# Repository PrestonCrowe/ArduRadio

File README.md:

# ArduRadio

This project includes 3 different projects that are encompased around Arduino-controlled radio chips. 

<br>

I've included the EAGLE PCB files for all of the boards and their respective BOMs besides the V2, but that one uses off the shelf parts so it shouldn't be too hard to make one.

So far, the only board that is 100% complete is the V2 board. I have yet to create any code for the boards. 

TODO
------
Please check the the Projects page on this GitHub page.

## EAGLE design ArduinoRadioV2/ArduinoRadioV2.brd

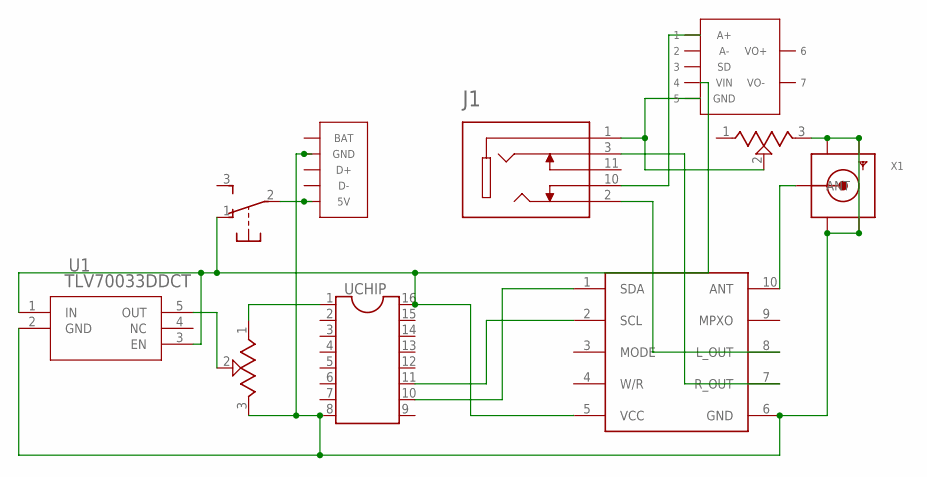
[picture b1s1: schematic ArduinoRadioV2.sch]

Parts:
IC1: UCHIP
J1: SJ1-3525N; CUI_SJ1-3525N
S1: EG1213
TEA5767: TEA5767BREAKOUT; TEA5767MM2
TUNE: 3352T-1-103LF; TRIM_3352T-1-103LF
U1: TLV70033DDCT; DDC5
U$1: AMP
U$2: MICROLIPO
VOL: 3352T-1-103LF; TRIM_3352T-1-103LF
X1: SMACONNECTOR; SMA90_DIP

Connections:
5V: IC1.16 (V_EXT), S1.1 (O), TEA5767.5 (VCC), U1.1 (IN), U1.3 (EN), U$1.VIN (4)
AIN: J1.10, U$1.A+ (1)
ANT: TEA5767.10 (ANT), X1.ANTENNA (ANT)
GND: IC1.8 (GND), TEA5767.6 (GND), TUNE.3 (CW), U1.2 (GND), U$2.P$1 (GND), U$2.P$2 (GND), U$2.P$3 (GND), U$2.P$4 (GND), U$2.P$8 (GND), VOL.3 (CW), X1.GND1, X1.GND2, X1.GND3, X1.GND4
LO: J1.2, TEA5767.8 (L_OUT)
unnamed: IC1.1 (D1/A1), TUNE.1 (CCW)
RO: J1.3, TEA5767.7 (R_OUT)
SCL: IC1.11 (D11), TEA5767.2 (SCL)
SDA: IC1.10 (D10), TEA5767.1 (SDA)
TUNE: TUNE.2 (WIPER), U1.5 (OUT)
VOL: J1.1, U$1.GND (5), VOL.2 (WIPER)
VS: S1.2, U$2.P$5 (5V)

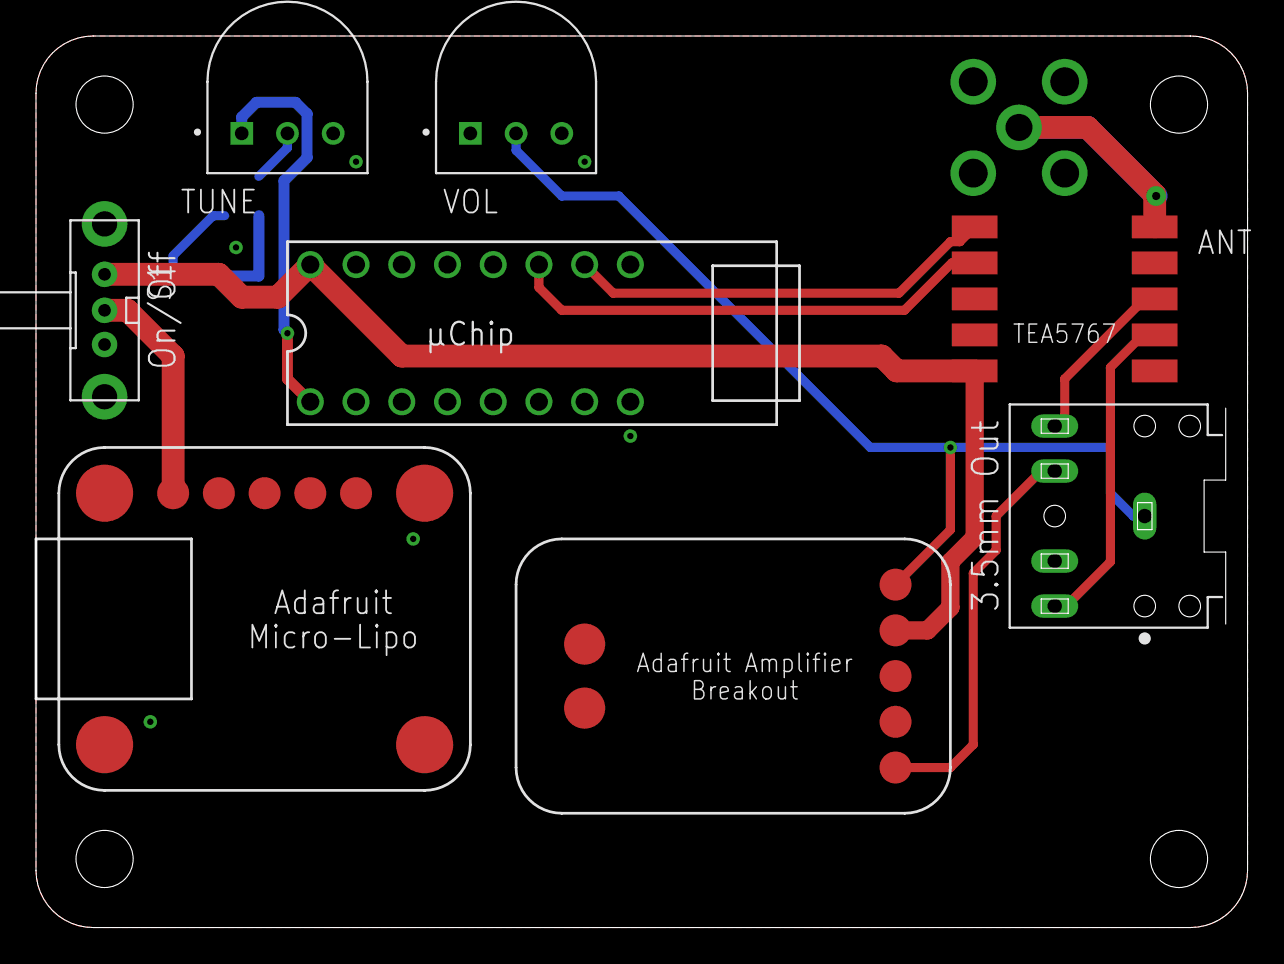
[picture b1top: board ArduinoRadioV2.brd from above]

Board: 2 copper layers, 67.3 x 49.5 mm, 10 parts (1 on the bottom side), 12 nets.

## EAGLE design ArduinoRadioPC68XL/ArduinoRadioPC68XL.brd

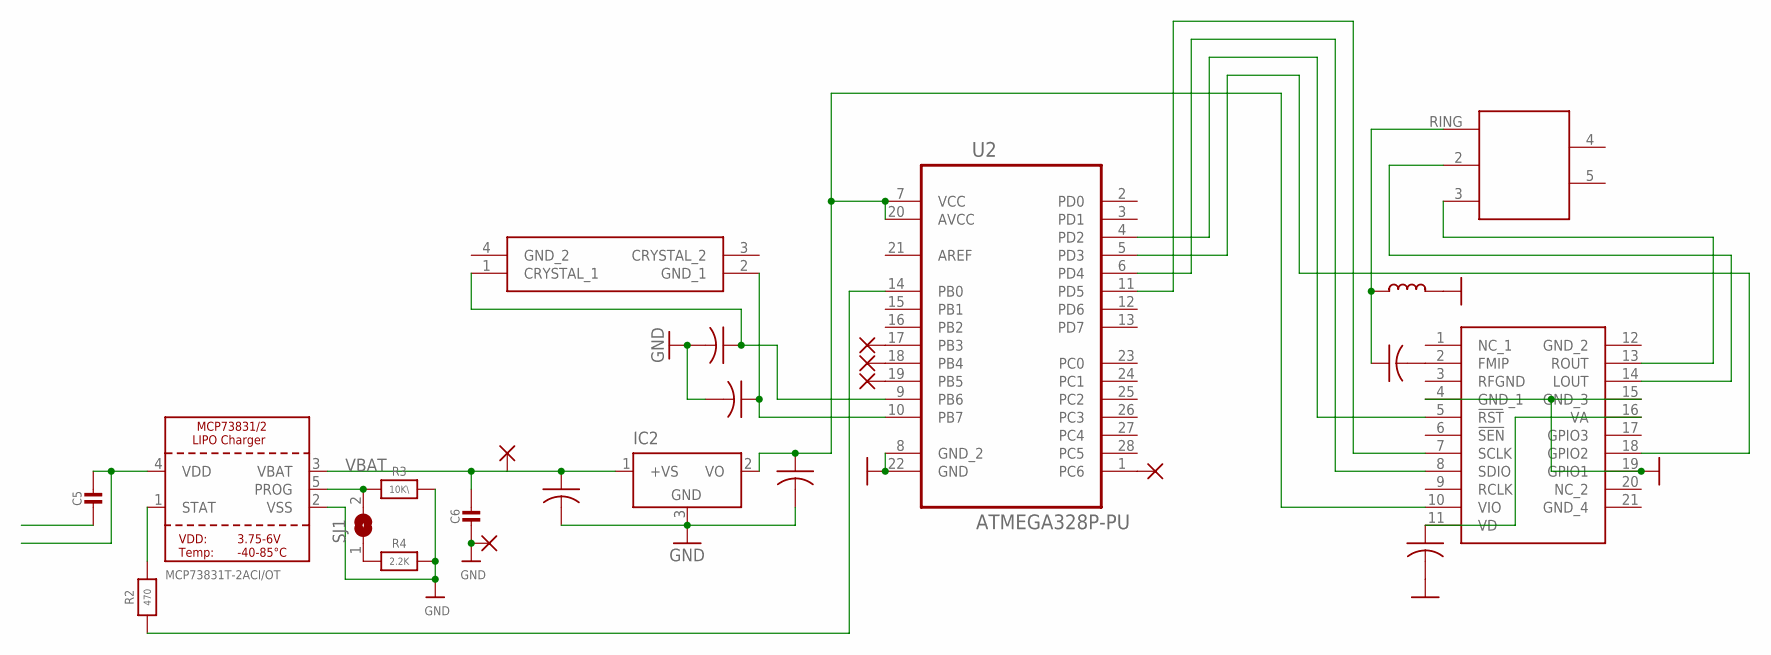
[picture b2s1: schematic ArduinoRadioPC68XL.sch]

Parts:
C1, C2: 10pF; C0402
C3: 47uf; C1206
C4: 47uF; C1206
C5, C6: 10µF; 0805-NO@1
C7: 22nF; C0603
C8: 100pF; C1206
IC2: LM50; SOT23
IC3: SI4703-C19-GM; SI4703C19GM
L1: L_0603; L0603
PAD1, PAD2: WIREPADSMD1,27-254; SMD1,27-2,54
PAD3, PAD4, PAD5, PAD6: SMD2; SMD1,27-2,54
R2: 470; 0603-NO
R3: 10K\; 0603-NO
R4: 2.2K; 0603-NO
SJ1: SOLDERJUMPER; SOLDERJUMPER_ARROW_NOPASTE
U1: MCP73831T-2ACI/OT; SOT23-5
U2: ATMEGA328P-PU; DIP254P762X457-28
U$1: STX-3542-5N-G-TR
Y1: ABM3B-8.000MHZ-10-1-U-T; ABM3B

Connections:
3V3: C4.1, IC2.2 (VO), IC3.10 (VIO), U2.7 (VCC), U2.20 (AVCC)
5V: C5.1, U1.4 (VDD)
ANT: C8.1, L1.2, U$1.RING
GND: C1.2, C2.2, C3.2, C4.2, C5.2, C6.2, C7.2, IC2.3 (GND), IC3.4 (GND_1), IC3.15 (GND_3), IC3.19 (GPIO1), L1.1, PAD2.1, R3.2, R4.2, U1.2 (VSS), U2.8 (GND_2), U2.22 (GND)
GPIO2: IC3.18 (GPIO2), U2.5 (PD3)
LOUT: IC3.14 (LOUT), U$1.2
MISO: PAD5.1, U2.18 (PB4)
MOSI: PAD6.1, U2.17 (PB3)
unnamed: R4.1, SJ1.1
unnamed: C8.2, IC3.2 (FMIP)
PROG: R3.1, SJ1.2, U1.5 (PROG)
RESET: PAD3.1, U2.1 (PC6)
ROUT: IC3.13 (ROUT), U$1.3
RST: IC3.5 (!RST), U2.4 (PD2)
SCK: PAD4.1, U2.19 (PB5)
SCLK: IC3.7 (SCLK), U2.11 (PD5)
SDIO: IC3.8 (SDIO), U2.6 (PD4)
STAT: R2.1, R2.2, U1.1 (STAT), U2.14 (PB0)
VBAT: C3.1, C6.1, C7.1, IC2.1 (+VS), IC3.11 (VD), IC3.16 (VA), PAD1.1, U1.3 (VBAT)
XTAL1: C1.1, U2.10 (PB7), Y1.2 (GND_1)
XTAL2: C2.1, U2.9 (PB6), Y1.1 (CRYSTAL_1)

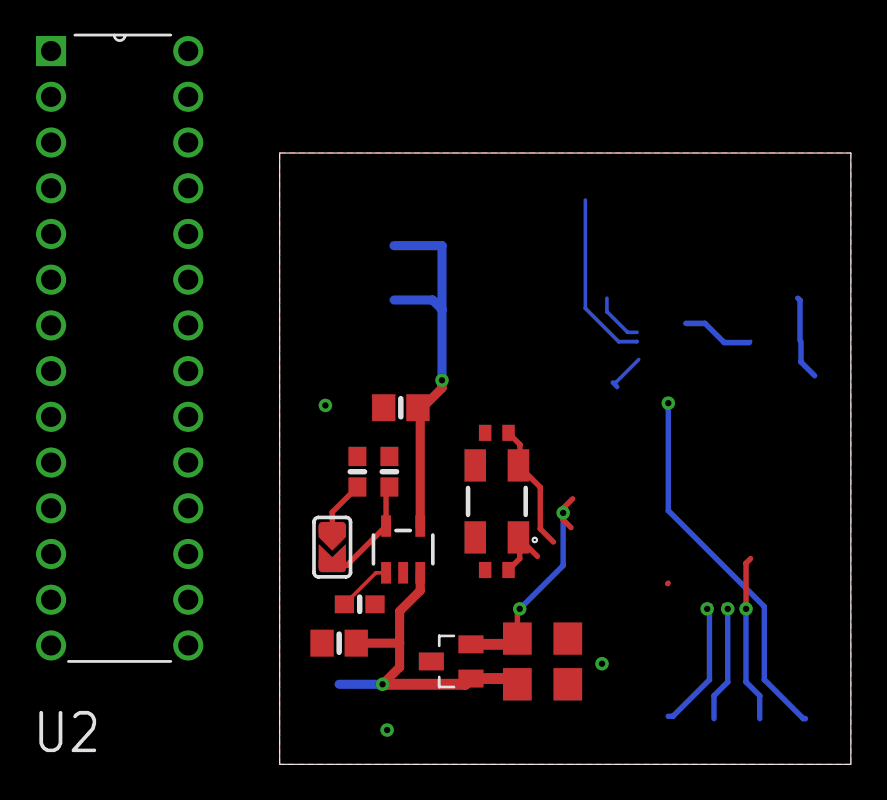
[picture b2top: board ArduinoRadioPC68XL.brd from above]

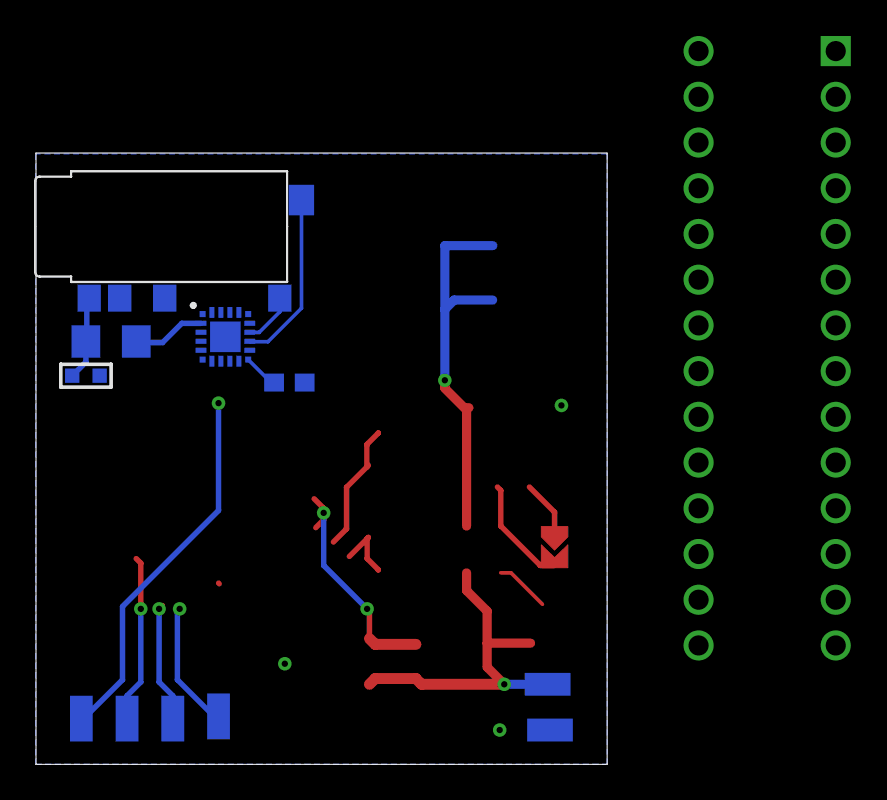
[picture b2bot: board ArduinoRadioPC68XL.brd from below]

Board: 2 copper layers, 31.7 x 34.0 mm, 25 parts (11 on the bottom side), 21 nets.

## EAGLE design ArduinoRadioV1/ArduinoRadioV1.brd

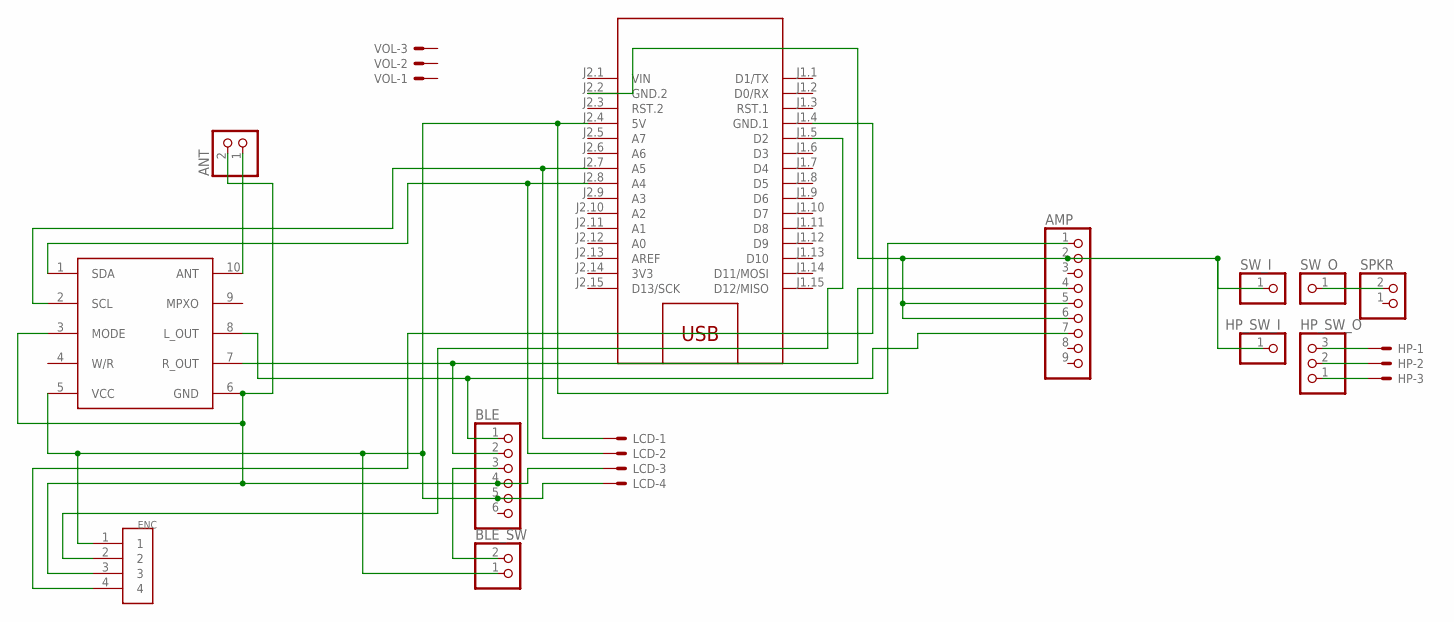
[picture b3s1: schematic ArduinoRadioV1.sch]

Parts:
AMP: PINHD-1X9; 1X09-BIG
ANT: JST_2PIN-THM; JST-PH-2-THM
BLE: PINHD-1X6; 1X06
BLE_SW: JST_2PIN-THM; JST-PH-2-THM
ENC: 1X4-BIG; 1X04-BIG
HP: JST-XH-03-PIN-ROUND-PAD; JST-XH-03-PACKAGE-ROUND-PAD
HP_SW_I: PINHD-1X1; 1X01
HP_SW_O: PINHD-1X3; 1X03
LCD: JST-XH-04-PIN-ROUND-PAD; JST-XH-04-PACKAGE-ROUND-PAD
M1: ARDUINO-NANO-3.0
SPKR: JST_2PIN-THM; JST-PH-2-THM
SW_I: PINHD-1X1; 1X01
SW_O: PINHD-1X1; 1X01
TEA5767: TEA5767BREAKOUT; TEA5767MM2
VOL: JST-XH-03-PIN-ROUND-PAD; JST-XH-03-PACKAGE-ROUND-PAD

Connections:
3V3: M1.J2.14 (3V3)
ANT: ANT.1 (2), TEA5767.10 (ANT)
D2: ENC.2, M1.J1.5 (D2)
GND: ANT.2 (1), BLE.4, ENC.3, LCD.3, TEA5767.3 (MODE), TEA5767.6 (GND)
HP_GND: HP.1, HP_SW_O.3
L: HP.3, HP_SW_O.1
L_OUT: AMP.7, BLE.1, TEA5767.8 (L_OUT)
unnamed: SPKR.2 (1), SW_O.1
unnamed: BLE.3, BLE_SW.2 (1)
unnamed: ENC.4, M1.J1.4 (GND.1)
R: HP.2, HP_SW_O.2
R_OUT: AMP.2, AMP.4, AMP.5, AMP.6, BLE.2, HP_SW_I.1, M1.J2.2 (GND.2), SW_I.1, TEA5767.7 (R_OUT)
SCL: LCD.1, M1.J2.7 (A5), TEA5767.2 (SCL)
SDA: LCD.2, M1.J2.8 (A4), TEA5767.1 (SDA)
VCC: AMP.1, BLE.5, BLE_SW.1 (2), ENC.1, LCD.4, M1.J2.4 (5V), TEA5767.5 (VCC)
VIN: M1.J2.1 (VIN)

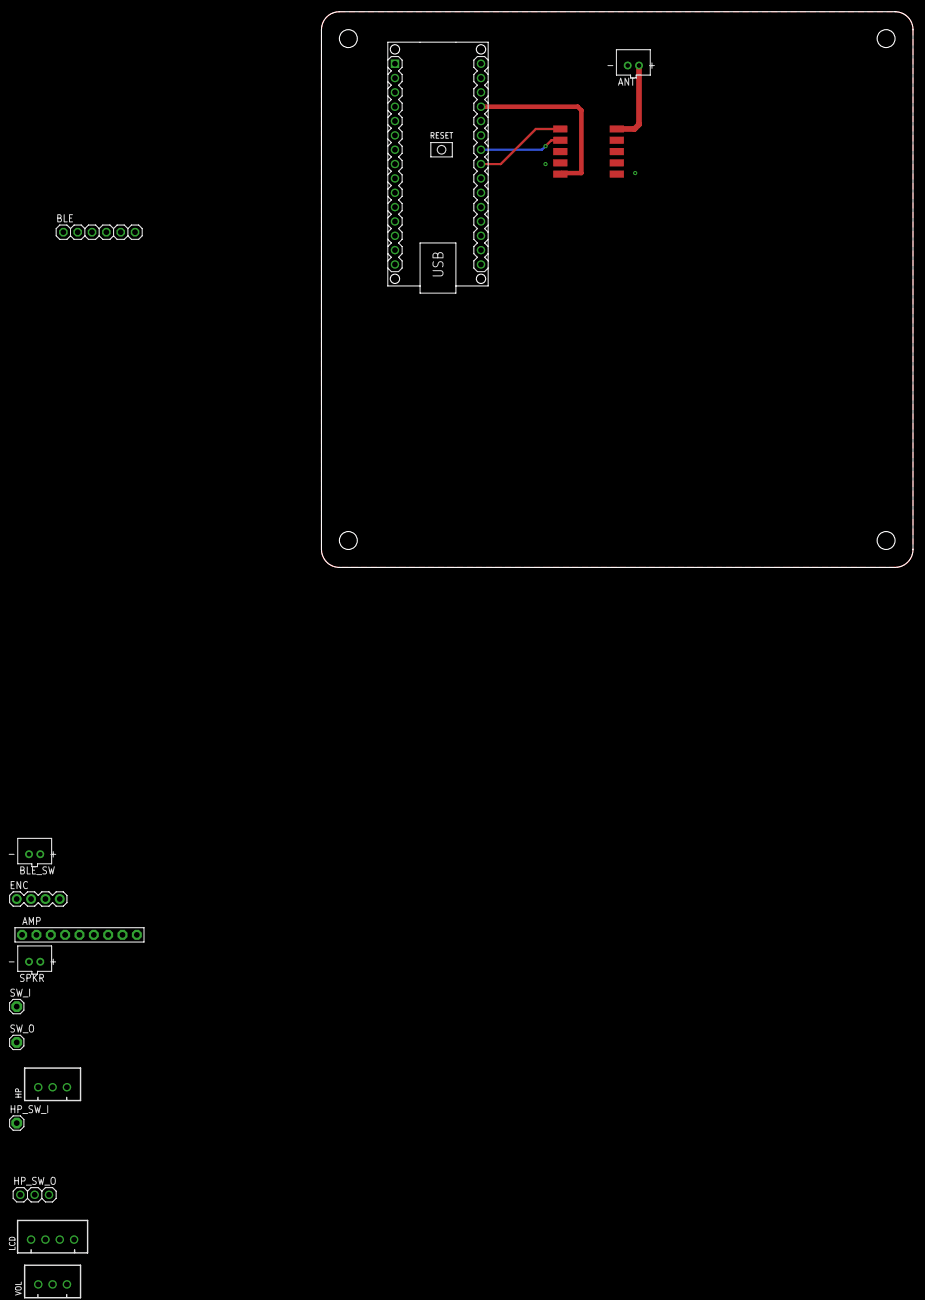
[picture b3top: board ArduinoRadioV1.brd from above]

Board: 2 copper layers, 104.8 x 98.4 mm, 15 parts (0 on the bottom side), 14 nets.

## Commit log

2020-06-24 Write README.md
2020-06-24 Add files
2020-06-24 Doing some organization
2020-09-01 Added design for CB radio footprint
2020-12-29 Create LICENSE
2021-03-31 Wipe V1 off the face of this earth
    V1 really sucked, I didn't have a BOM, it wasn't finished, blah blah blah. It was one of my first PCB designs, and I didn't want to finish something I wouldn't make.
2021-04-05 Finish routing V3 board
2021-04-05 Deleting auto-gen files that I didn't catch
2021-04-05 Create BOM for V2 and label parts

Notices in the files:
parts and their libraries:
microbuilder: This work is placed in the public domain, and may be freely used for commercial and non-commercial work with the following conditions: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
rc-master-smd: Copyright (C) 2007, Bob Starr
